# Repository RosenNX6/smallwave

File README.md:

# smallwave

<span>

</span>

The smallwave is a 34 key wireless split keyboard with a e-paper style display.
This design ultimately comes from the popular [Sweep](https://github.com/davidphilipbarr/Sweep) layout but was built by modifying the [Urchin](https://github.com/duckyb/uchin) design and inspired by many aspects of the [Flipper](https://github.com/benvallack/the-flipper) and Corne layout.

## Hardware List
#### Required Parts
- 1× smallwave PCB (files can be found in the gerbers folder)
- 2× nice!nano
- 2× Lipo battery
- 48× Mill-max machined pins
- 2× Pair of female headers
- 34× Kailh choc hotswap sockets
- 34× Kailh choc v1 switches
- 34× Keycaps
- 34× SMD diodes

#### Optional Parts
- 2x nice!view
- 12x Vinyl self adhesive pads
- 2x Magnetic type C cable
- 1x Dual port USB wall charger

#### Itemized Parts Receipt (v1.0 build)
| Quantity | Item | Source | Cost |
| :---: | --- | --- | --- |
| 2 | nice!nano | typeractive.xyz | $50.00 |
| 2 | nice!view | typeractive.xyz | $40.00 |
| 40 | SMD Diode | typeractive.xyz | $3.00 |
| 40 | Kailh Hotswap Sockets | typeractive.xyz | $6.00 |
| 40 | Kailh Low Profile Choc Switches (Pro Red) | typeractive.xyz | $28.00 |
| 4 | MBK Choc Keycaps (1u convex) | typeractive.xyz | $2.00 |
| 2 | MBK Choc Keycaps (1u homing) | typeractive.xyz | $1.00 |
| 30 | MBK Choc Keycaps (1u) | typeractive.xyz | $10.50 |
| 4 | Machine Sockets and Pins | typeractive.xyz | $13.00 |
| 2 | Reset Button | typeractive.xyz | $1.50 |
| 2 | Battery Jack (black) | typeractive.xyz | $2.00 |
| 2 | Power Switch | typeractive.zyz | $1.50 |
| 2 | Lithium Battery 110mAh (BLK PH 2.0mm) | typeractive.xyz | $8.00 |
| 5 | smallwave PCB | jlcpcb.com | $38.93 |
| 16 | Vinyl Self Adhesive Pads (round 3/8") | Ace Hardware | $4.99 |
| 2 | Magnetic Type C Cable | amazon.com | $14.99 |
| 1 | Anker PowerPort Mini Dual Port USB Wall Charger | amazon.com | $6.99 |

## Design Software
#### KiCad
PCB design, part locations, copper traces, and pads. This was a steep learning curve for me but the software was incredible once I got the hang of it.
#### AutoCAD
PCB shape (edge cuts). This can be done in KiCad but I am inexperienced with the software and felt much more comfortable drawing prototype shapes in a software I am more familiar with.
#### Inkscape
Used for making the PCB art through the use of SVG files. 
#### Github
Used for programming the keyboard in the ZMK language directly in the web browser. How cool is that? More on this below.

## Firmware
The smallwave utilizes the ZMK programming language. To view, download, or edit the zmk programming used for this project, visit the [zmk-config-smallwave repository](https://github.com/rosennx6/zmk-config-smallwave).

## Inspiration/Credits
This build was inspired by the Ferris Sweep, Ben Vallack's Flipper, and Duccio's Urchin. I started this project with zero knowledge of keyboards, PCBs, or programming but, along with browsing [r/ErgoMechKeyboards](https://www.reddit.com/r/ErgoMechKeyboards/) the videos below were very helpful for me in getting started.
- [You Won't Beleive How Effective This Keyboard Layout Is](https://youtu.be/8wZ8FRwOzhU?si=EpPOE7a2gVTnpphz)
- [A Tiny, Ultra-Affordable Keyboard You Can Build Yourself!](https://youtu.be/JqpBKuEVinw?si=qibRUbN7NvYlW7R7)
- [How to make a SWEEP KEYBOARD (beginner friendly!)](https://youtu.be/fBPu7AyDtkM?si=BP1d7TfXiWL5cw6Q)
- [URCHIN Ergonomic Keyboard Build](https://youtu.be/CHSh1-dJq24?si=E14KtWMmz5-_V5mR)
- [PCB Art - A Step By Step Tutorial](https://youtu.be/vD6es-Y4LLc?si=0AxjCWdZhJgSs7d_)
- [Beginner ZMK Tutorial - How to make and modify your ZMK keymap](https://youtu.be/Kx8F4xI5yno?si=BYquHvFE0kq7FGJF)
- [How to Set Up ZMK Firmware From Scratch](https://youtu.be/O_urj-rF3bQ?si=-QcN1Bxoi7COPyYP)

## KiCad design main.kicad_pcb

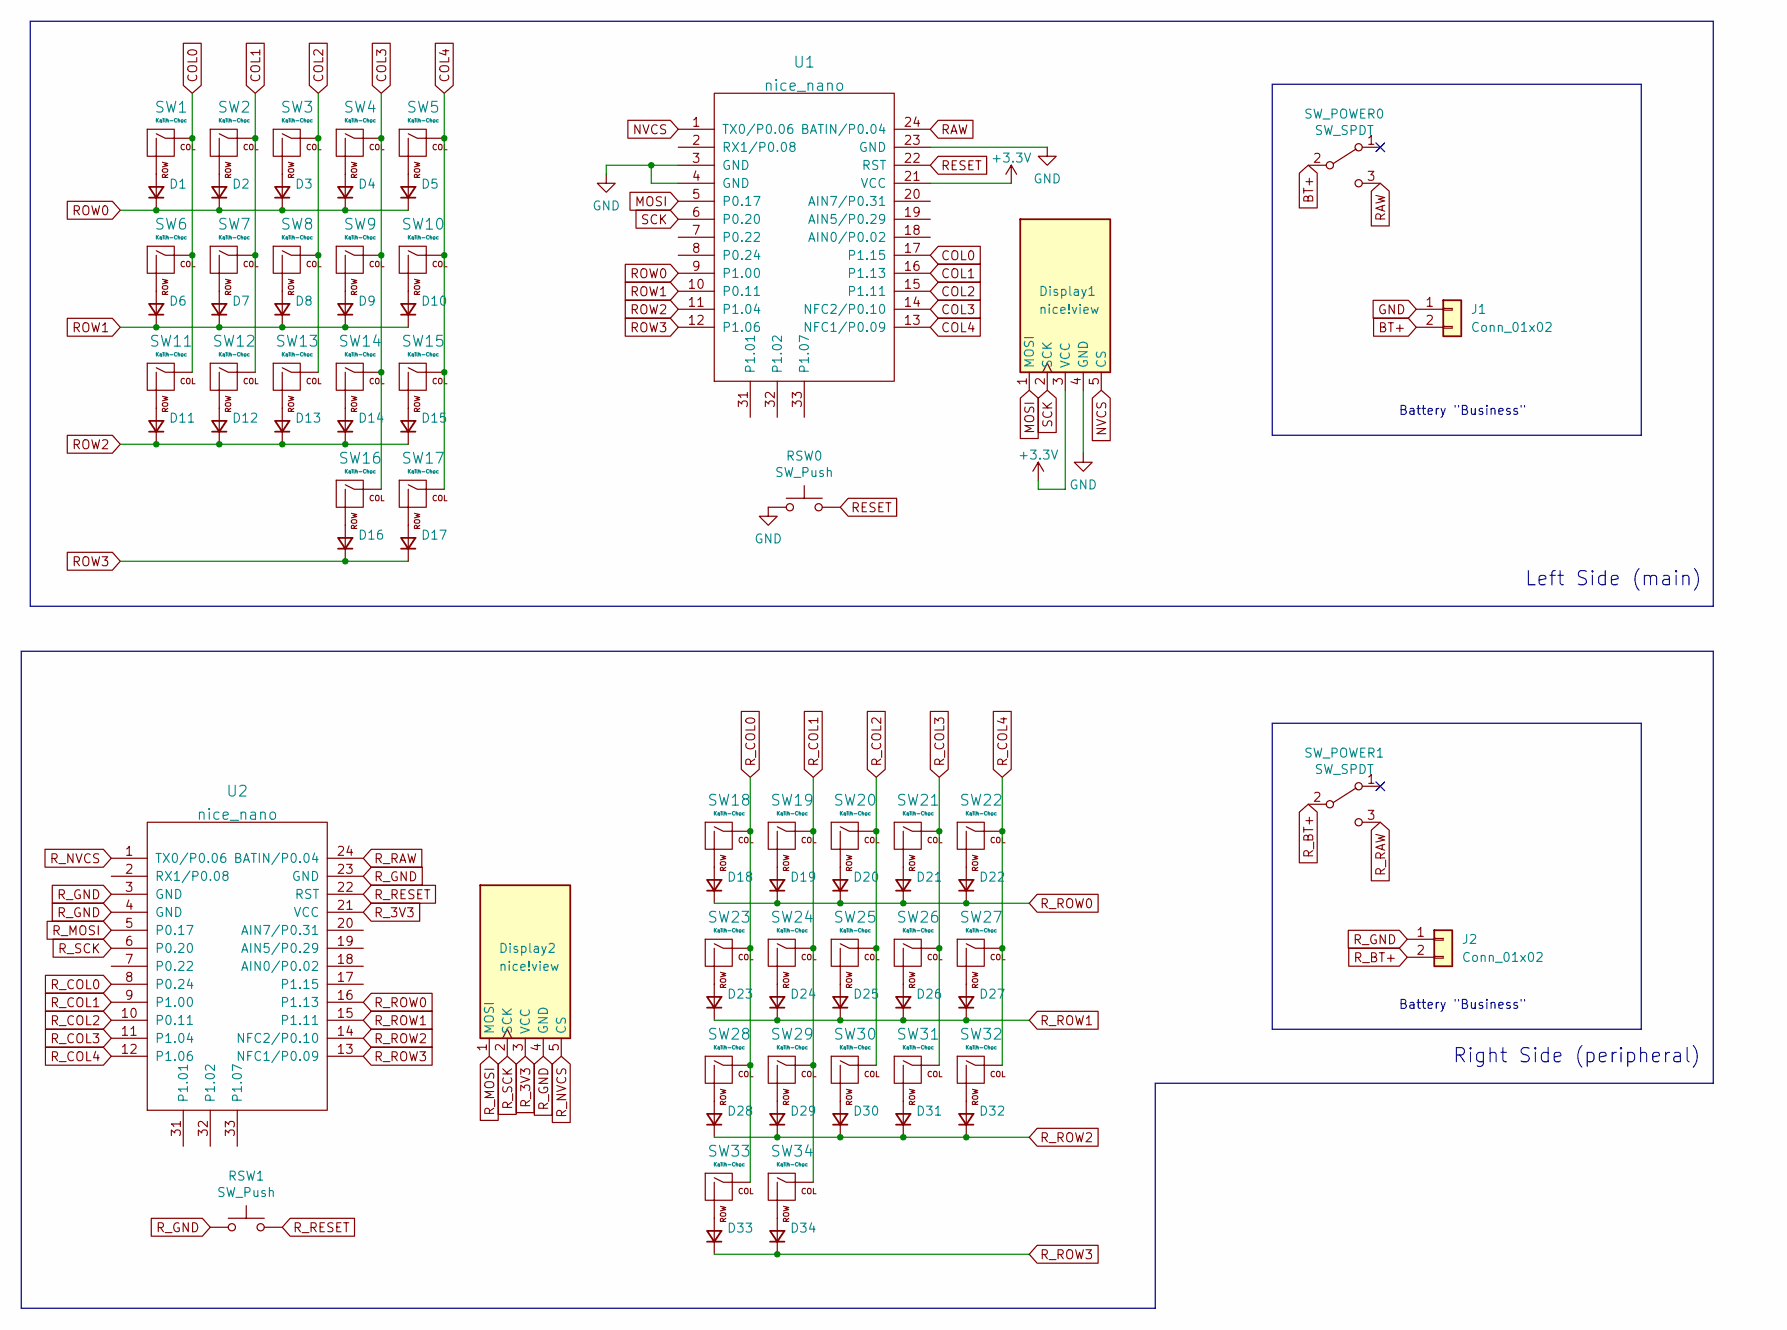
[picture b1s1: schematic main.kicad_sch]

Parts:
D1, D2, D3, D4, D5, D6, D7, D8, D9, D10, D11, D12, D13, D14, D15, D16, D17, D18, D19, D20, D21, D22, D23, D24, D25, D26, D27, D28, D29, D30, D31, D32, D33, D34: diode; SMD_Diode_Tiny
Display1, Display2: nice!view; nice_view
J1, J2: Conn_01x02; JST_PH_S2B-PH-K_1x02_P2.00mm_Horizontal
RSW0, RSW1: SW_Push; SW_RESET
SW1, SW2, SW3, SW4, SW5, SW6, SW7, SW8, SW9, SW10, SW11, SW12, SW13, SW14, SW15, SW16, SW17, SW18, SW19, SW20, SW21, SW22, SW23, SW24, SW25, SW26, SW27, SW28, SW29, SW30, SW31, SW32, SW33, SW34: Kailh-Choc; SW_Hotswap_Kailh_Choc_V1_tweaked
SW_POWER0, SW_POWER1: SW_SPDT; smt-slider-switch
U1, U2: nice_nano

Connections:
+3V3: Display1.3 (VCC), U1.21 (VCC)
BT+: J1.2, SW_POWER0.2 (B)
COL0: SW1.1 (COL), SW6.1 (COL), SW11.1 (COL), U1.17 (P1.15)
COL1: SW2.1 (COL), SW7.1 (COL), SW12.1 (COL), U1.16 (P1.13)
COL2: SW3.1 (COL), SW8.1 (COL), SW13.1 (COL), U1.15 (P1.11)
COL3: SW4.1 (COL), SW9.1 (COL), SW14.1 (COL), SW16.1 (COL), U1.14 (NFC2/P0.10)
COL4: SW5.1 (COL), SW10.1 (COL), SW15.1 (COL), SW17.1 (COL), U1.13 (NFC1/P0.09)
GND: Display1.4 (GND), J1.1, RSW0.1, U1.3 (GND), U1.4 (GND), U1.23 (GND)
MOSI: Display1.1 (MOSI), U1.5 (P0.17)
NVCS: Display1.5 (CS), U1.1 (TX0/P0.06)
unnamed: D1.2 (A), SW1.2 (ROW)
unnamed: D2.2 (A), SW2.2 (ROW)
unnamed: D3.2 (A), SW3.2 (ROW)
unnamed: D4.2 (A), SW4.2 (ROW)
unnamed: D5.2 (A), SW5.2 (ROW)
unnamed: D6.2 (A), SW6.2 (ROW)
unnamed: D7.2 (A), SW7.2 (ROW)
unnamed: D8.2 (A), SW8.2 (ROW)
unnamed: D9.2 (A), SW9.2 (ROW)
unnamed: D10.2 (A), SW10.2 (ROW)
unnamed: D11.2 (A), SW11.2 (ROW)
unnamed: D12.2 (A), SW12.2 (ROW)
unnamed: D13.2 (A), SW13.2 (ROW)
unnamed: D14.2 (A), SW14.2 (ROW)
unnamed: D15.2 (A), SW15.2 (ROW)
unnamed: D16.2 (A), SW16.2 (ROW)
unnamed: D17.2 (A), SW17.2 (ROW)
unnamed: D18.2 (A), SW18.2 (ROW)
unnamed: D19.2 (A), SW19.2 (ROW)
unnamed: D20.2 (A), SW20.2 (ROW)
unnamed: D21.2 (A), SW21.2 (ROW)
unnamed: D22.2 (A), SW22.2 (ROW)
unnamed: D23.2 (A), SW23.2 (ROW)
unnamed: D24.2 (A), SW24.2 (ROW)
unnamed: D25.2 (A), SW25.2 (ROW)
unnamed: D26.2 (A), SW26.2 (ROW)
unnamed: D27.2 (A), SW27.2 (ROW)
unnamed: D28.2 (A), SW28.2 (ROW)
unnamed: D29.2 (A), SW29.2 (ROW)
unnamed: D30.2 (A), SW30.2 (ROW)
unnamed: D31.2 (A), SW31.2 (ROW)
unnamed: D32.2 (A), SW32.2 (ROW)
unnamed: D33.2 (A), SW33.2 (ROW)
unnamed: D34.2 (A), SW34.2 (ROW)
RAW: SW_POWER0.3 (C), U1.24 (BATIN/P0.04)
RESET: RSW0.2, U1.22 (RST)
ROW0: D1.1 (K), D2.1 (K), D3.1 (K), D4.1 (K), D5.1 (K), U1.9 (P1.00)
ROW1: D6.1 (K), D7.1 (K), D8.1 (K), D9.1 (K), D10.1 (K), U1.10 (P0.11)
ROW2: D11.1 (K), D12.1 (K), D13.1 (K), D14.1 (K), D15.1 (K), U1.11 (P1.04)
ROW3: D16.1 (K), D17.1 (K), U1.12 (P1.06)
R_3V3: Display2.3 (VCC), U2.21 (VCC)
R_BT+: J2.2, SW_POWER1.2 (B)
R_COL0: SW18.1 (COL), SW23.1 (COL), SW28.1 (COL), SW33.1 (COL), U2.8 (P0.24)
R_COL1: SW19.1 (COL), SW24.1 (COL), SW29.1 (COL), SW34.1 (COL), U2.9 (P1.00)
R_COL2: SW20.1 (COL), SW25.1 (COL), SW30.1 (COL), U2.10 (P0.11)
R_COL3: SW21.1 (COL), SW26.1 (COL), SW31.1 (COL), U2.11 (P1.04)
R_COL4: SW22.1 (COL), SW27.1 (COL), SW32.1 (COL), U2.12 (P1.06)
R_GND: Display2.4 (GND), J2.1, RSW1.1, U2.3 (GND), U2.4 (GND), U2.23 (GND)
R_MOSI: Display2.1 (MOSI), U2.5 (P0.17)
R_NVCS: Display2.5 (CS), U2.1 (TX0/P0.06)
R_RAW: SW_POWER1.3 (C), U2.24 (BATIN/P0.04)
R_RESET: RSW1.2, U2.22 (RST)
R_ROW0: D18.1 (K), D19.1 (K), D20.1 (K), D21.1 (K), D22.1 (K), U2.16 (P1.13)
R_ROW1: D23.1 (K), D24.1 (K), D25.1 (K), D26.1 (K), D27.1 (K), U2.15 (P1.11)
R_ROW2: D28.1 (K), D29.1 (K), D30.1 (K), D31.1 (K), D32.1 (K), U2.14 (NFC2/P0.10)
R_ROW3: D33.1 (K), D34.1 (K), U2.13 (NFC1/P0.09)
R_SCK: Display2.2 (SCK), U2.6 (P0.20)
SCK: Display1.2 (SCK), U1.6 (P0.20)

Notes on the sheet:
Right Side (peripheral)
Battery "Business"
Left Side (main)

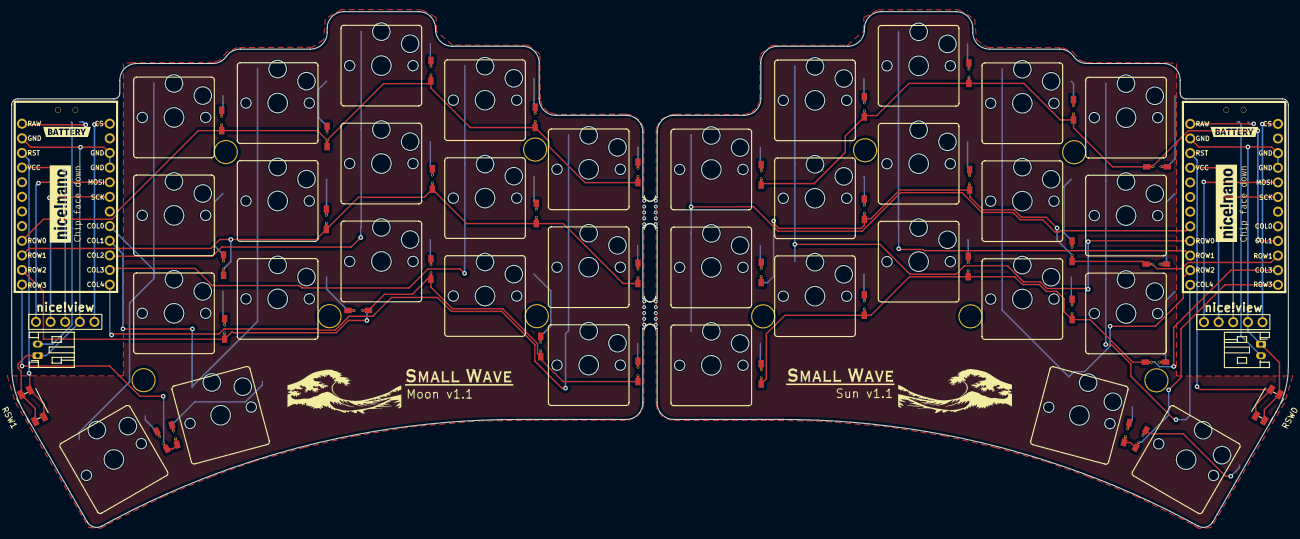
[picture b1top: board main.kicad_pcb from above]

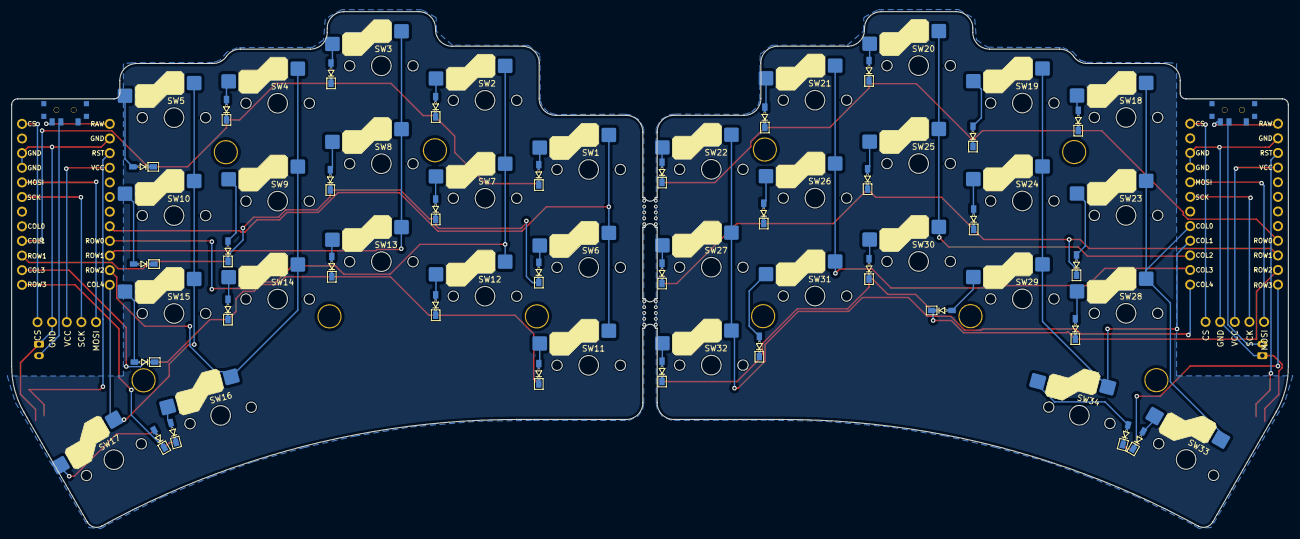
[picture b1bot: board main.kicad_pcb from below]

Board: 2 copper layers, 221.6 x 89.5 mm, 96 parts (9 on the bottom side), 68 nets.

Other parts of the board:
H1, H1#2, H2, H2#2, H3, H3#2, H4, H4#2, H4#3, H4#4: M2 Hole; M2_hole_4.2mm
kibuzzard-636588C8, kibuzzard-636588C8#2: G***; kibuzzard-636588C8
kibuzzard-636592CC: G***; kibuzzard-636592CC
kibuzzard-6365884B: G***; kibuzzard-6365884B
kibuzzard-63658865: G***; kibuzzard-63658865
kibuzzard-63659296: G***; kibuzzard-63659296
mouse-bite-2mm-slot, mouse-bite-2mm-slot#2: VAL**; mouse-bite-5mm-slot-with-space-for-track

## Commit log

2023-11-23 Add files via upload
    Added photo of completed v1.0 build.
2023-11-23 Create hello
